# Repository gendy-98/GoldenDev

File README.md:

# UART Echo Example

(See the README.md file in the upper level 'examples' directory for more information about examples.)

This example demonstrates how to utilize UART interfaces of ESP32 by echoing back to the sender any data received on
UART1.

## How to use example

### Hardware Required

The example can be run on any ESP32 development board connected to a PC with a single USB cable for flashing and
monitoring. The external interface should have 3.3V outputs. You may use e.g. 3.3V compatible USB-to-Serial dongle.

### Setup the Hardware

Connect the external serial interface to the ESP32 board as follows.

  | ESP32 Interface | #define | ESP32 Pin | External UART Pin |
  | --- | --- | --- | --- |
  | Transmit Data (TxD) | ECHO_TEST_TXD | GPIO4 | RxD |
  | Receive Data (RxD) | ECHO_TEST_RXD | GPIO5 | TxD |
  | Ground | n/a | GND | GND |

Optionally, you can set-up and use a serial interface that has RTS and CTS signals in order to verify that the
hardware control flow works. Connect the extra signals according to the following table, configure both extra pins in
the example code by replacing existing `UART_PIN_NO_CHANGE` macros with the appropriate pin numbers and configure
UART1 driver to use the hardware flow control by setting `.flow_ctrl = UART_HW_FLOWCTRL_CTS_RTS` and adding
`.rx_flow_ctrl_thresh = 122`.

  | ESP32 Interface | #define | ESP32 Pin | External UART Pin |
  | --- | --- | --- | --- |
  | Request to Send (RTS) | ECHO_TEST_RTS | GPIO18 | CTS |
  | Clear to Send (CTS) | ECHO_TEST_CTS | GPIO19 | RTS |

### Configure the project

```
idf.py menuconfig
```

### Build and Flash

Build the project and flash it to the board, then run monitor tool to view serial output:

```
idf.py -p PORT flash monitor
```

(To exit the serial monitor, type ``Ctrl-]``.)

See the Getting Started Guide for full steps to configure and use ESP-IDF to build projects.

## Example Output

Type some characters in the terminal connected to the external serial interface. As result you should see echo in the
terminal which is used for flashing and monitoring. You can verify if the echo indeed comes from ESP32 by
disconnecting either `TxD` or `RxD` pin: no characters will appear when typing.

## Troubleshooting

You are not supposed to see the echo in the terminal which is used for flashing and monitoring, but in the other one
which is connected to UART1.

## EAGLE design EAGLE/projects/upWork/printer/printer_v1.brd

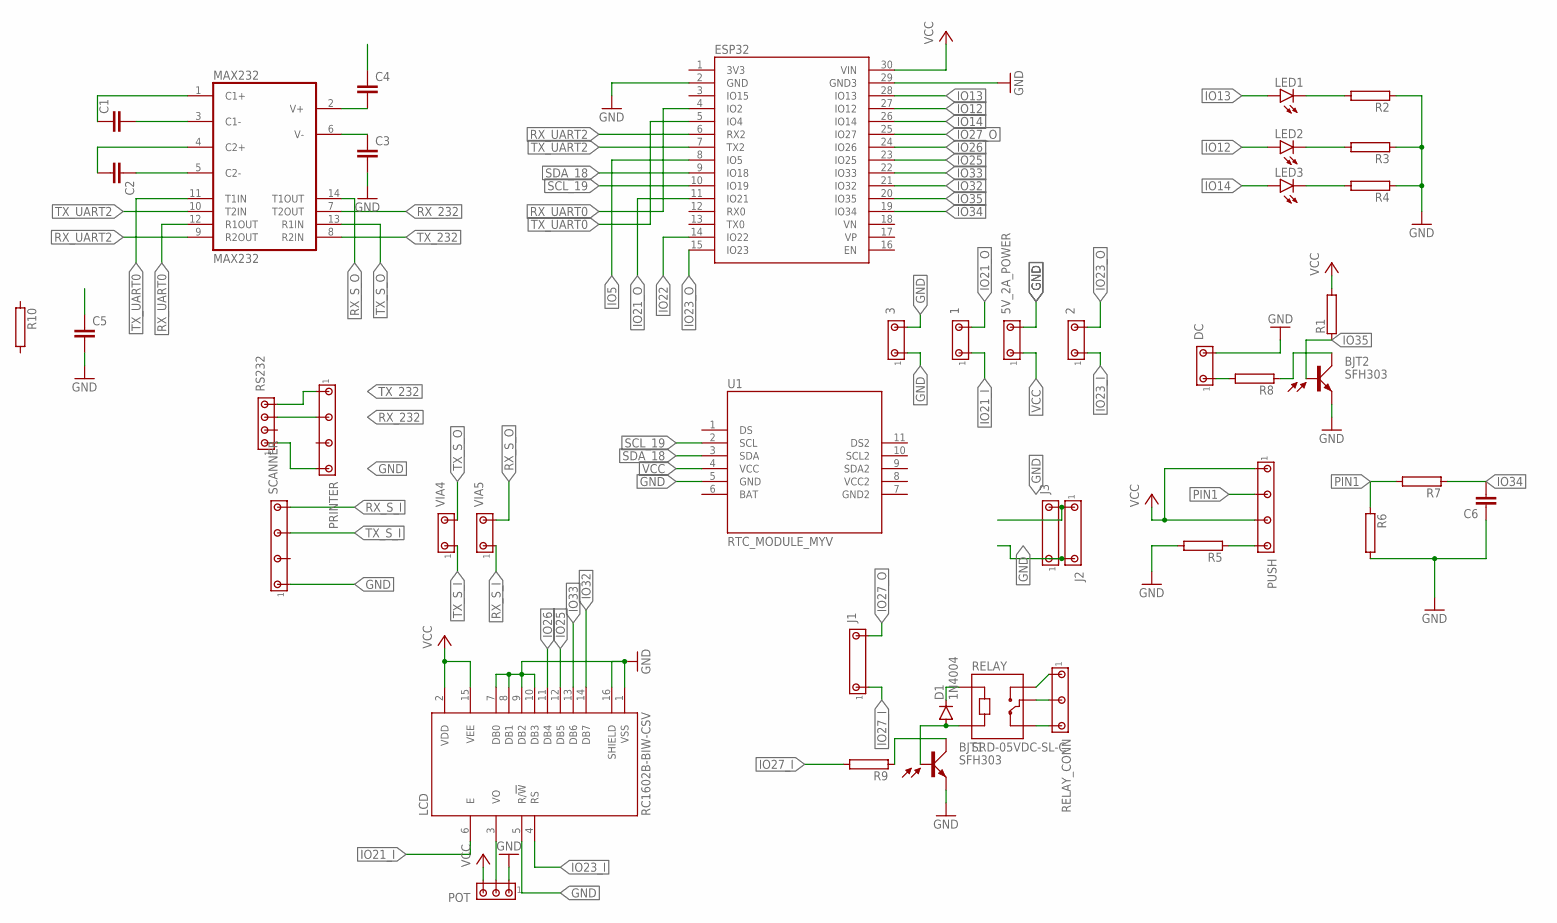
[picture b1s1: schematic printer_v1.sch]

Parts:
1, 2, 3, 5V_2A_POWER: MTA03-100_MYV; 10X03MTA_MYV
BJT1, BJT2: SFH303
C1, C2, C3, C4, C5, C6: C-EU025-024X044; C025-024X044
D1: 1N4004; DO41-10
DC: MTA03-100_MYV; 10X03MTA_MYV
ESP32: MODULE_ESP32_MYV; MODULE_ESP32-DEVKITC-MYV
J1, J2, J3: MTA02-LARGE_MYVSPACE1; 10X02MTA_LARGE_MYV
LCD: RC1602B-BIW-CSV; LCD_RC1602B-BIW-CSV
LED1, LED2, LED3: LED3MM
MAX232: MAX232; DIL16
POT: MTA03-100; 10X03MTA
PRINTER: MTA07-100_MYV; 10X07MTA_MYV
PUSH: MTA07-100_MYV; 10X07MTA_MYV
R1, R2, R3, R4, R5, R6, R7, R8, R9, R10: RHPS58; HPS58
RELAY: SRD-05VDC-SL-C; RELAY_SRD-05VDC-SL-C
RELAY_CONN: MTA05-156_MYVSPACE1; 10X05MTA_MYV
RS232: MTA04-100; 10X04MTA
SCANNER: MTA07-100_MYV; 10X07MTA_MYV
U1: RTC_MODULE_MYV; RTC_MYV
VIA4, VIA5: MTA03-100_MYV; 10X03MTA_MYV

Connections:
3V3: ESP32.1 (3V3)
GND: 3.1, 3.3, 5V_2A_POWER.3, BJT1.1 (E), BJT2.1 (E), C3.2, C5.2, C6.1, DC.3, ESP32.2 (GND), ESP32.29 (GND3), J2.1, J2.5, J3.1, J3.5, LCD.1 (VSS), LCD.5 (R/!W), LCD.7 (DB0), LCD.8 (DB1), LCD.9 (DB2), LCD.10 (DB3), LCD.16 (SHIELD), MAX232.15 (GND), POT.1, PRINTER.7, R2.1, R3.1, R4.1, R5.2, R6.2, RS232.1, SCANNER.1, U1.5 (GND)
IO5: ESP32.8 (IO5)
IO12: ESP32.27 (IO12), LED2.A
IO13: ESP32.28 (IO13), LED1.A
IO14: ESP32.26 (IO14), LED3.A
IO21_I: 1.1, LCD.6 (E)
IO21_O: 1.3, ESP32.11 (IO21)
IO22: ESP32.14 (IO22)
IO23_I: 2.1, LCD.4 (RS)
IO23_O: 2.3, ESP32.15 (IO23)
IO25: ESP32.23 (IO25), LCD.12 (DB5)
IO26: ESP32.24 (IO26), LCD.11 (DB4)
IO27_I: J1.1, R9.2
IO27_O: ESP32.25 (IO27), J1.5
IO32: ESP32.21 (IO32), LCD.14 (DB7)
IO33: ESP32.22 (IO33), LCD.13 (DB6)
IO34: C6.2, ESP32.19 (IO34), R7.1
IO35: BJT2.3 (B), ESP32.20 (IO35), R1.1
unnamed: C1.1, MAX232.1 (C1+)
unnamed: C1.2, MAX232.3 (C1-)
unnamed: C2.1, MAX232.5 (C2-)
unnamed: C2.2, MAX232.4 (C2+)
unnamed: C3.1, MAX232.6 (V-)
unnamed: C4.2, MAX232.2 (V+)
unnamed: D1.C, RELAY.A1
unnamed: BJT1.2 (C), R9.1
unnamed: RELAY.NC, RELAY_CONN.5
unnamed: RELAY.COM, RELAY_CONN.3
unnamed: RELAY.NO, RELAY_CONN.1
unnamed: LED1.K (C), R2.2
unnamed: LED2.K (C), R3.2
unnamed: BJT2.2 (C), R8.1
unnamed: LED3.K (C), R4.2
unnamed: LCD.3 (VO), POT.2
unnamed: DC.1, R8.2
unnamed: BJT1.3 (B), D1.A, RELAY.A2
unnamed: PUSH.7, R5.1
PIN1: PUSH.3, R6.1, R7.2
RX_232: MAX232.7 (T2OUT), PRINTER.3, RS232.3
RX_S_I: SCANNER.7, VIA5.1
RX_S_O: MAX232.14 (T1OUT), VIA5.3
RX_UART0: ESP32.4 (IO2), MAX232.12 (R1OUT)
RX_UART2: ESP32.6 (RX2), MAX232.9 (R2OUT)
SCL_19: ESP32.10 (IO19), U1.2 (SCL)
SDA_18: ESP32.9 (IO18), U1.3 (SDA)
TX_232: MAX232.8 (R2IN), PRINTER.1, RS232.4
TX_S_I: SCANNER.5, VIA4.1
TX_S_O: MAX232.13 (R1IN), VIA4.3
TX_UART0: ESP32.5 (IO4), MAX232.11 (T1IN)
TX_UART2: ESP32.7 (TX2), MAX232.10 (T2IN)
VCC: 5V_2A_POWER.1, ESP32.30 (VIN), LCD.2 (VDD), LCD.15 (VEE), MAX232.16 (VCC), POT.3, PUSH.1, PUSH.5, R1.2, U1.4 (VCC)

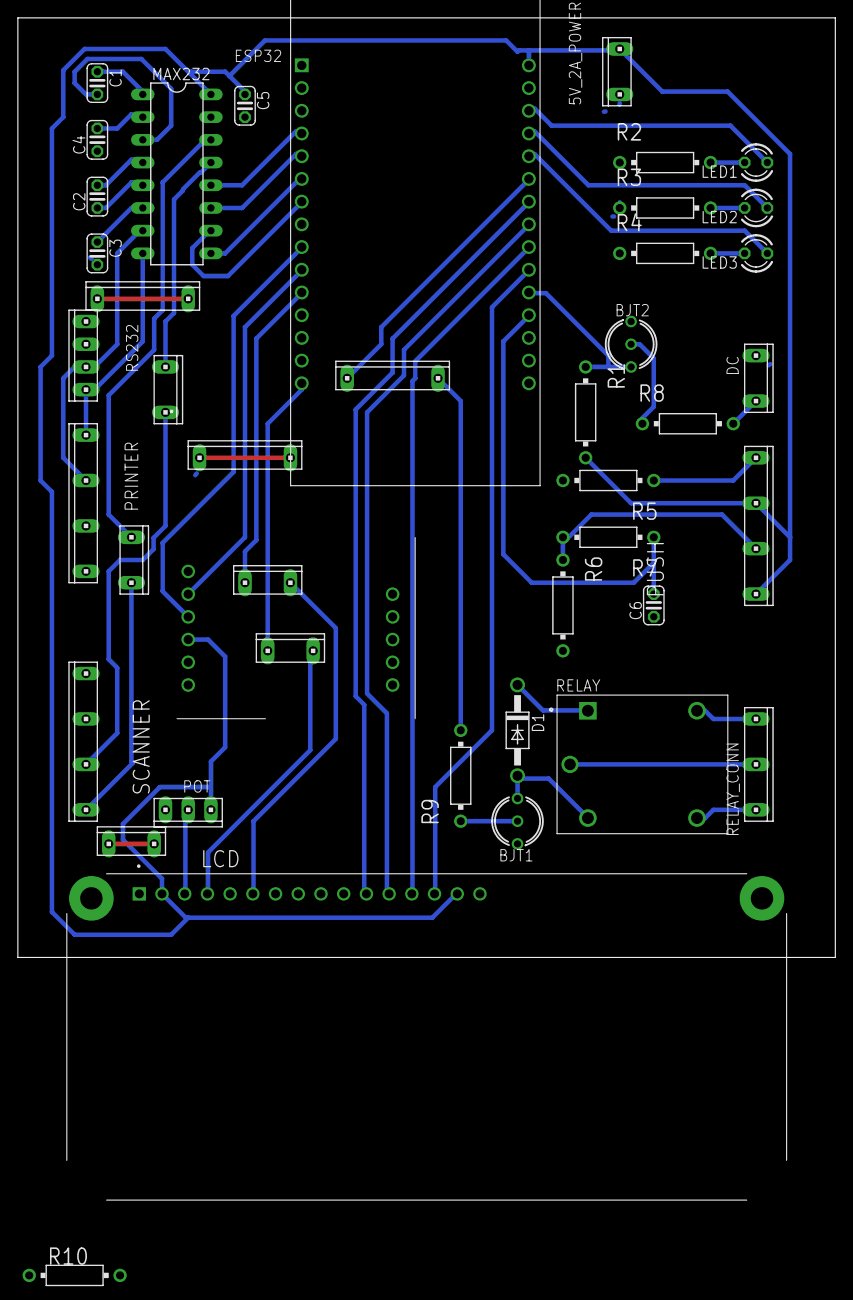
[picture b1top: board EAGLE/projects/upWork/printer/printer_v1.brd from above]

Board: 2 copper layers, 91.4 x 105.1 mm, 43 parts (0 on the bottom side), 49 nets.

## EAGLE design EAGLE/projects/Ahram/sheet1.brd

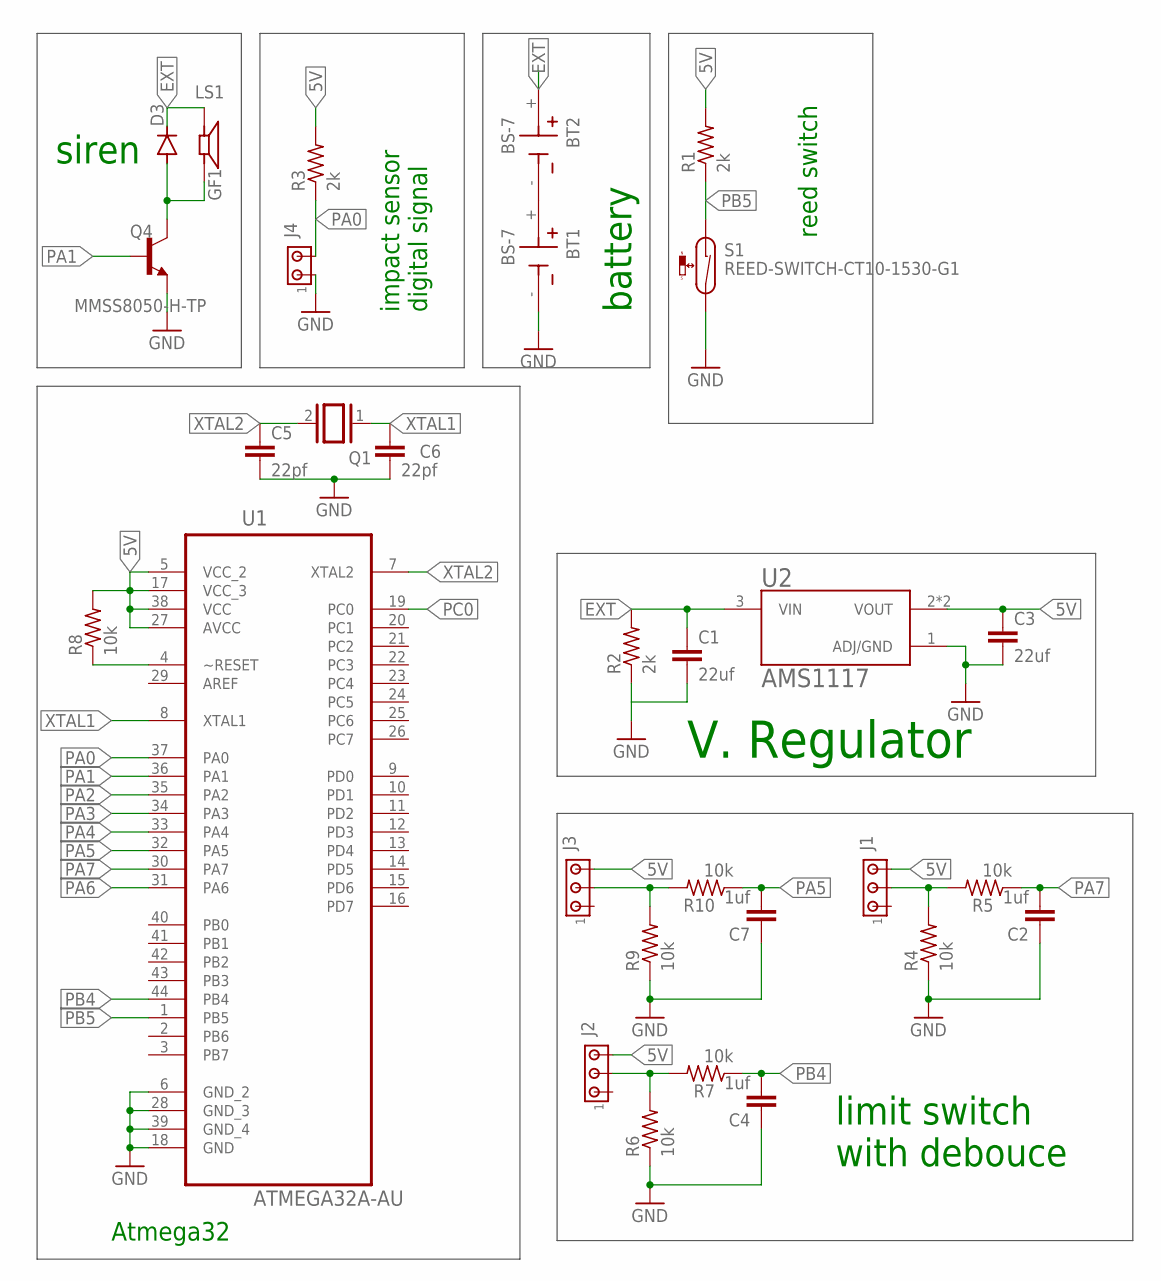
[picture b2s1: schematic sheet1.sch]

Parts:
BT1, BT2: BS-7; BAT_BS-7
C1, C3: 22uf; C1206
C2, C4, C7: 1uf; C1206
C5, C6: 22pf; C1206
D3: GF1; SMA-DO214AC
J1, J2, J3: MTA03-100; 10X03MTA
J4: MTA02-100; 10X02MTA
LS1: CEP-1152; CUI_CEP-1152
Q1: XTAL/S; QS
Q4: MMSS8050-H-TP; TRANS_MMSS8050-H-TP
R1, R2, R3: 2k; R1206
R4, R5, R6, R7, R8, R9, R10: 10k; R1206
S1: REED-SWITCH-CT10-1530-G1; CT10-G1
U1: ATMEGA32A-AU; QFP80P1200X1200X120-44N
U2: AMS1117; SOT229P700X180-4N

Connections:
5V: C3.1, J1.3, J2.3, J3.3, R1.2, R3.2, R8.2, U1.5 (VCC_2), U1.17 (VCC_3), U1.27 (AVCC), U1.38 (VCC), U2.2 (VOUT), U2.4 (VOUT)
EXT: BT2.+, C1.1, D3.K (C), LS1.1, R2.2, U2.3 (VIN)
GND: BT1.-, C1.2, C2.1, C3.2, C4.1, C5.2, C6.2, C7.1, J4.1, Q4.2 (E), R2.1, R4.1, R6.1, R9.1, S1.2, U1.6 (GND_2), U1.18 (GND), U1.28 (GND_3), U1.39 (GND_4), U2.1 (ADJ/GND)
unnamed: J1.2, R4.2, R5.2
unnamed: BT1.+, BT2.-
unnamed: R8.1, U1.4 (~RESET)
unnamed: J3.2, R9.2, R10.2
unnamed: J2.2, R6.2, R7.2
unnamed: D3.A, LS1.2, Q4.3 (C)
PA0: J4.2, R3.1, U1.37 (PA0)
PA1: Q4.1 (B), U1.36 (PA1)
PA2: U1.35 (PA2)
PA3: U1.34 (PA3)
PA4: U1.33 (PA4)
PA5: C7.2, R10.1, U1.32 (PA5)
PA6: U1.31 (PA6)
PA7: C2.2, R5.1, U1.30 (PA7)
PB4: C4.2, R7.1, U1.44 (PB4)
PB5: R1.1, S1.1, U1.1 (PB5)
PC0: U1.19 (PC0)
XTAL1: C6.1, Q1.1, U1.8 (XTAL1)
XTAL2: C5.1, Q1.2, U1.7 (XTAL2)

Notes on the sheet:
V. Regulator
siren
impact sensor digital signal
battery
limit switch with debouce
reed switch
Atmega32

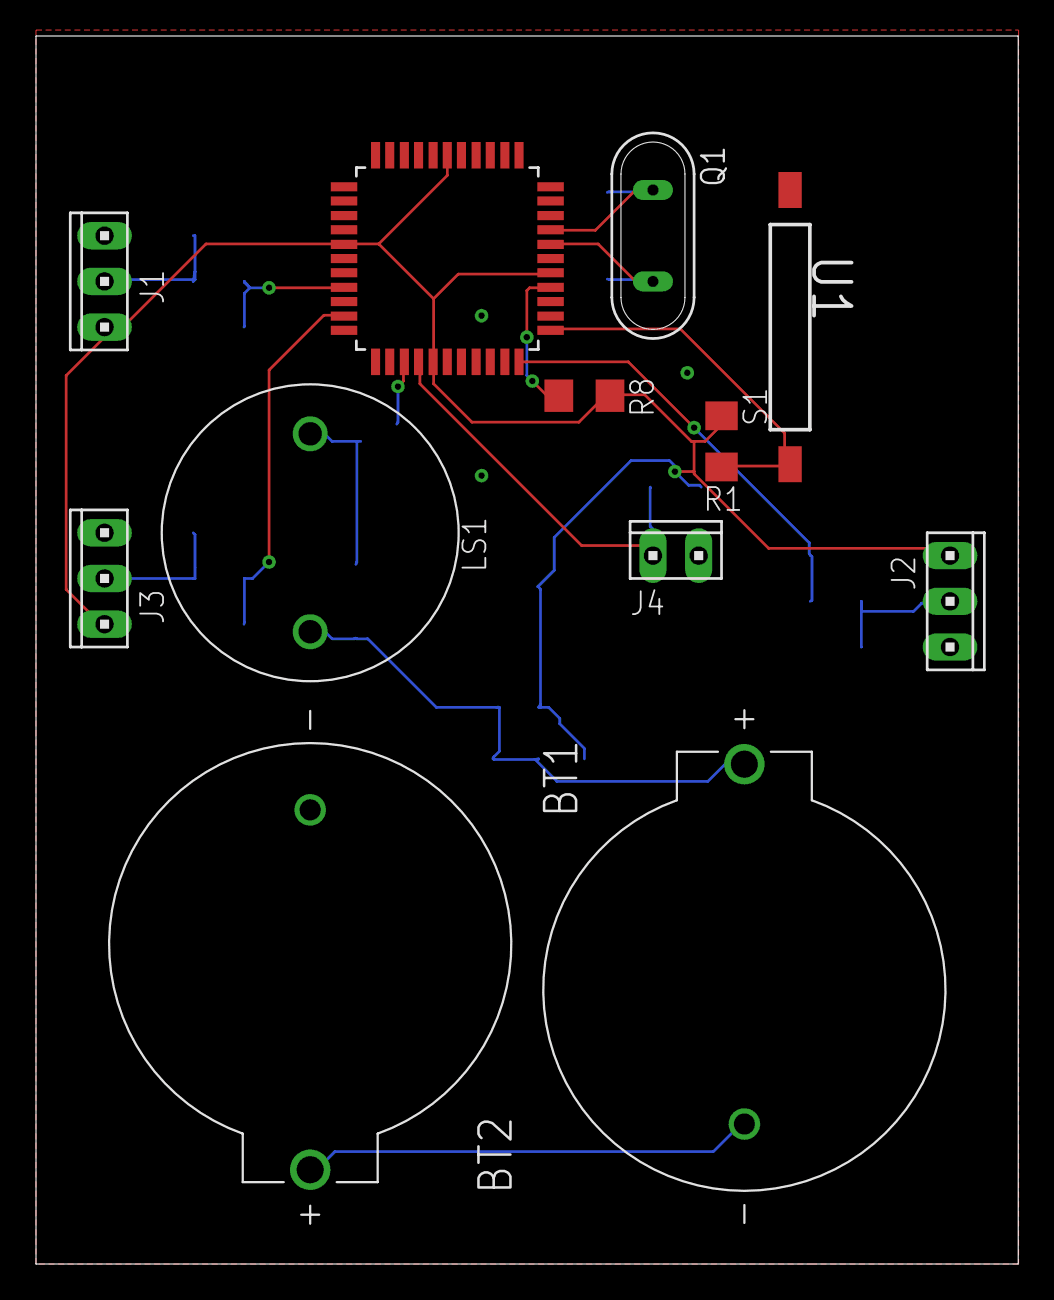
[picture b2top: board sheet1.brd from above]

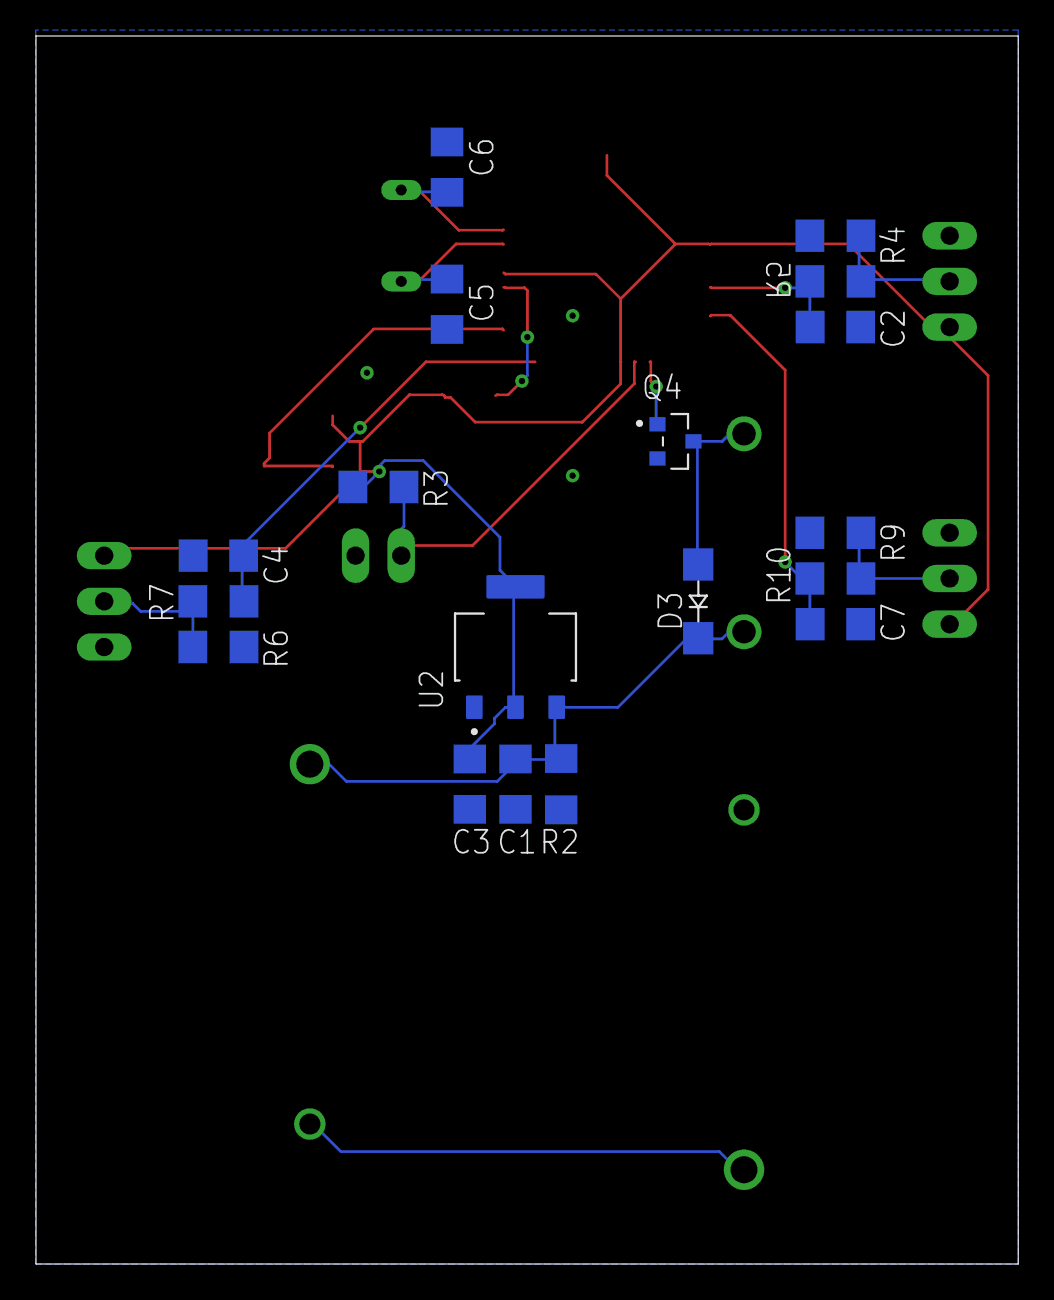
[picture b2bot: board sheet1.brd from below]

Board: 2 copper layers, 54.6 x 68.2 mm, 30 parts (18 on the bottom side), 17 nets.

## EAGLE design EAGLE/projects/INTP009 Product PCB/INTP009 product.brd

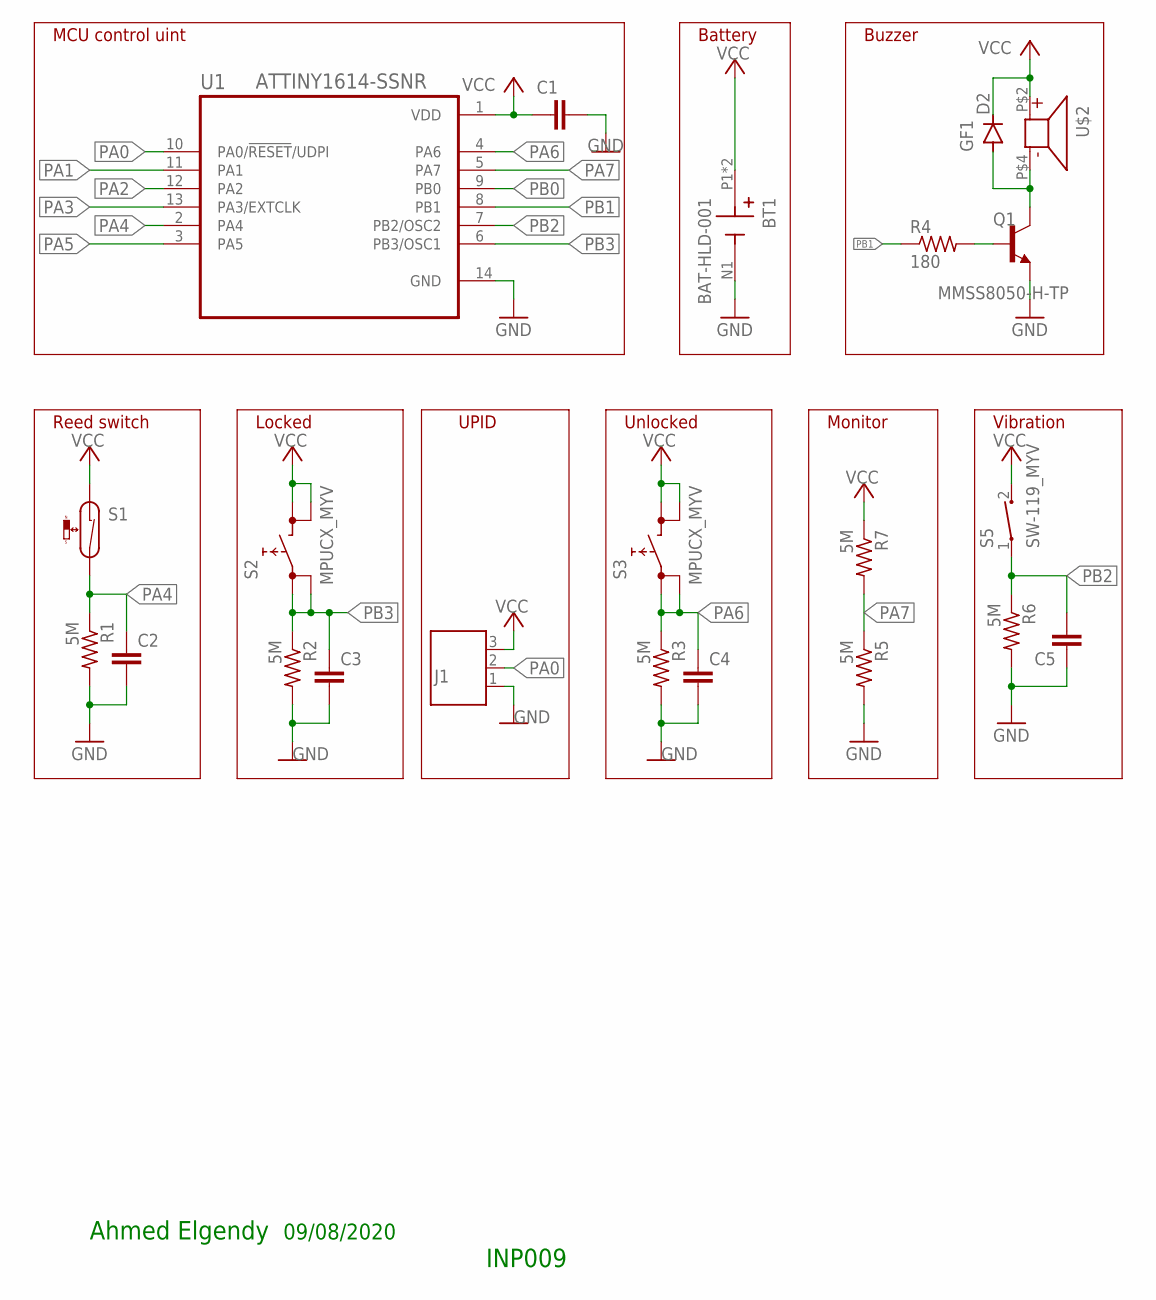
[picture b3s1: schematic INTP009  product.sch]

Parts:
BT1: BAT-HLD-001; BAT_BAT-HLD-001
C1, C2, C3, C4, C5: C-EUC0805K; C0805K
D2: GF1; SMA-DO214AC
J1: 691508110303
Q1: MMSS8050-H-TP; TRANS_MMSS8050-H-TP
R1, R2, R3, R5, R6, R7: 5M; M0805
R4: 180; M0805
S1: RI80SMDM-MYV; RI80SMDM-0510-J1
S2, S3: MPUCX_MYV
S5: SW-119_MYV; SW-119
U1: ATTINY1614-SSNR; SOIC127P600X175-14N
U$2: ST-A03BH_MYV

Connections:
GND: BT1.N1 (-), C1.2, C2.2, C3.2, C4.2, C5.1, J1.1, Q1.2 (E), R1.2, R2.2, R3.2, R5.2, R6.2, U1.14 (GND)
unnamed: D2.A, Q1.3 (C), U$2.P$4 (2)
unnamed: Q1.1 (B), R4.2
PA0: J1.2, U1.10 (PA0/!RESET!/UDPI)
PA1: U1.11 (PA1)
PA2: U1.12 (PA2)
PA3: U1.13 (PA3/EXTCLK)
PA4: C2.1, R1.1, S1.P$2 (2), U1.2 (PA4)
PA5: U1.3 (PA5)
PA6: C4.1, R3.1, S3.1, S3.2, U1.4 (PA6)
PA7: R5.1, R7.2, U1.5 (PA7)
PB0: U1.9 (PB0)
PB1: R4.1, U1.8 (PB1)
PB2: C5.2, R6.1, S5.1, U1.7 (PB2/OSC2)
PB3: C3.1, R2.1, S2.1, S2.2, U1.6 (PB3/OSC1)
VCC: BT1.P1 (+), BT1.P2 (+), C1.1, D2.K (C), J1.3, R7.1, S1.P$1 (1), S2.3, S2.4, S3.3, S3.4, S5.2, U1.1 (VDD), U$2.P$2 (1)

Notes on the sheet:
Ahmed Elgendy
09/08/2020
INP009
MCU control uint
Reed switch
Locked
Unlocked
Battery
Vibration
Buzzer
Monitor
UPID

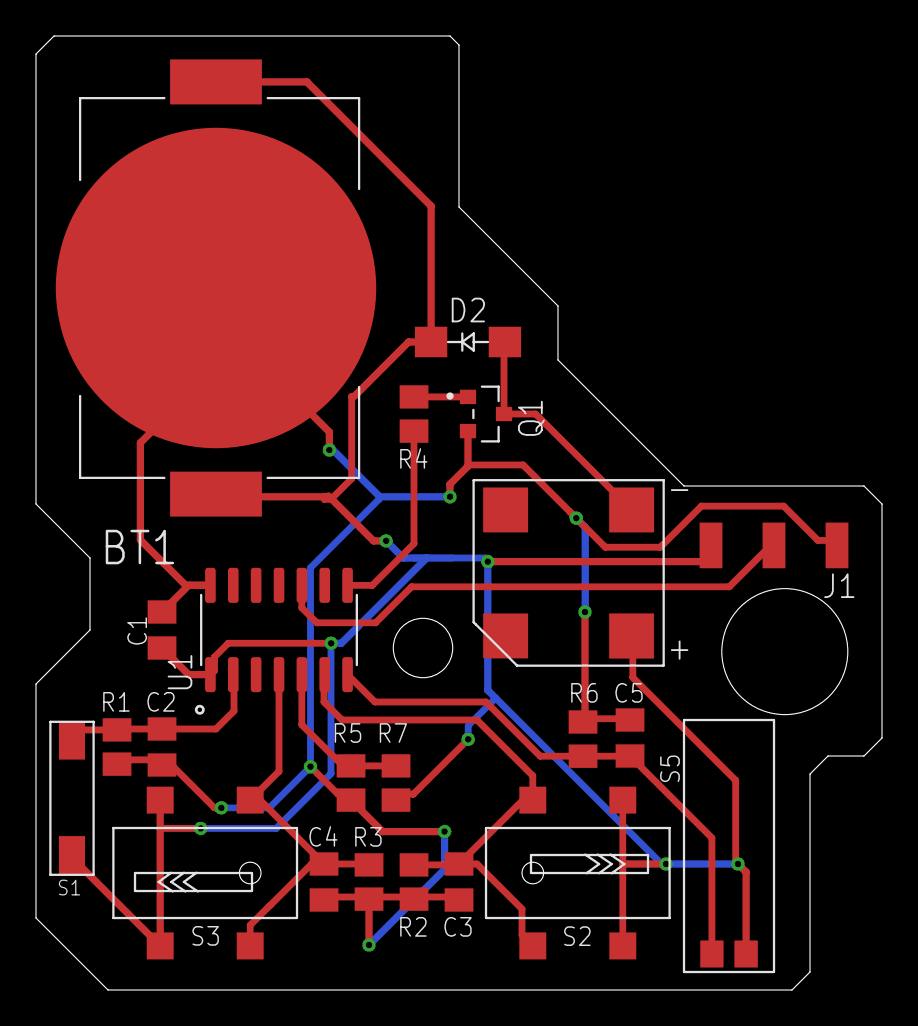
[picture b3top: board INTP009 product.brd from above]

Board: 2 copper layers, 47.0 x 53.0 mm, 22 parts (0 on the bottom side), 11 nets.

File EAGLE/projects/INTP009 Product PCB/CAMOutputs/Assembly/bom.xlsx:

Qty | Value | Device | Package | Parts | Description | ARROW_ELECTRONICS-PURCHASE-URL | AVAILABILITY | DESCRIPTION | DIGIKEY-PURCHASE-URL | MF | MOUSER-PURCHASE-URL | MP | PACKAGE | POPULARITY | PRICE | SPICEPREFIX
1 |  | 691508110303 | 691508110303 | J1 | WR-TBL Terminal block - serie 5081 - 3 Pins;=>Code : Con_TBL_Screw_PClamp_3.50_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
2 | 100nf | C-EUC0805K | C0805K | C1, C2, C3, C4, C5 | CAPACITOR, European symbol |  |  |  |  |  |  |  |  | 52 |  | C
3 | 180ohm | R-US_M0805 | M0805 | R4 | RESISTOR, American symbol |  |  |  |  |  |  |  |  | 45 |  | R
4 | 5M | R-US_M0805 | M0805 | R1, R2, R3, R5, R6, R7 | RESISTOR, American symbol |  |  |  |  |  |  |  |  | 45 |  | R
5 | ATTINY1614-SSNR | ATTINY1614-SSNR | SOIC127P600X175-14N | U1 | 20MHz, SOIC, 85C, Green, 14 SOIC .150in T/R | https://snapeda.com/shop?store=Arrow+Electronics&id=4817174 | Unavailable | IC MCU 8BIT 16KB FLASH 14SOIC | https://snapeda.com/shop?store=DigiKey&id=4817174 | Microchip Technology | https://snapeda.com/shop?store=Mouser&id=4817174 | ATTINY1614-SSNR | None |  | None
6 | BAT-HLD-001 | BAT-HLD-001 | BAT_BAT-HLD-001 | BT1 | Battery Retainer Coin, 20.0mm 1 Cell SMD (SMT) Tab Buy Part |  | Good | Battery Holder 1 Cells Phosphor Bronze Bulk | https://snapeda.com/shop?store=DigiKey&id=184402 | Linx Technologies | https://snapeda.com/shop?store=Mouser&id=184402 | BAT-HLD-001 | None |  | None
7 | GF1 | GF1 | SMA-DO214AC | D2 | DIODE |  |  |  |  |  |  |  |  | 2
8 | MMSS8050-H-TP | MMSS8050-H-TP | TRANS_MMSS8050-H-TP | Q1 | MMSS8050-H Series 25 V 1.5 A NPN Silicon Plastic-Encapsulate Transistor-SOT-23 |  | Unavailable | Bipolar _BJT_ Transistor NPN 25V 1.5A 100MHz 625mW Surface Mount SOT-23 |  | Micro Commercial |  | MMSS8050-H-TP | SOT-23 Micro Commercial |  | None
9 | MPUCX_MYV | MPUCX_MYV | MPUCX_MYV | S2, S3
10 | RI80SMDM-MYV | RI80SMDM-MYV | RI80SMDM-0510-J1 | S1
11 | ST-A03BH_MYV | ST-A03BH_MYV | ST-A03BH_MYV | U$2
12 | SW-119_MYV | SW-119_MYV | SW-119 | S5

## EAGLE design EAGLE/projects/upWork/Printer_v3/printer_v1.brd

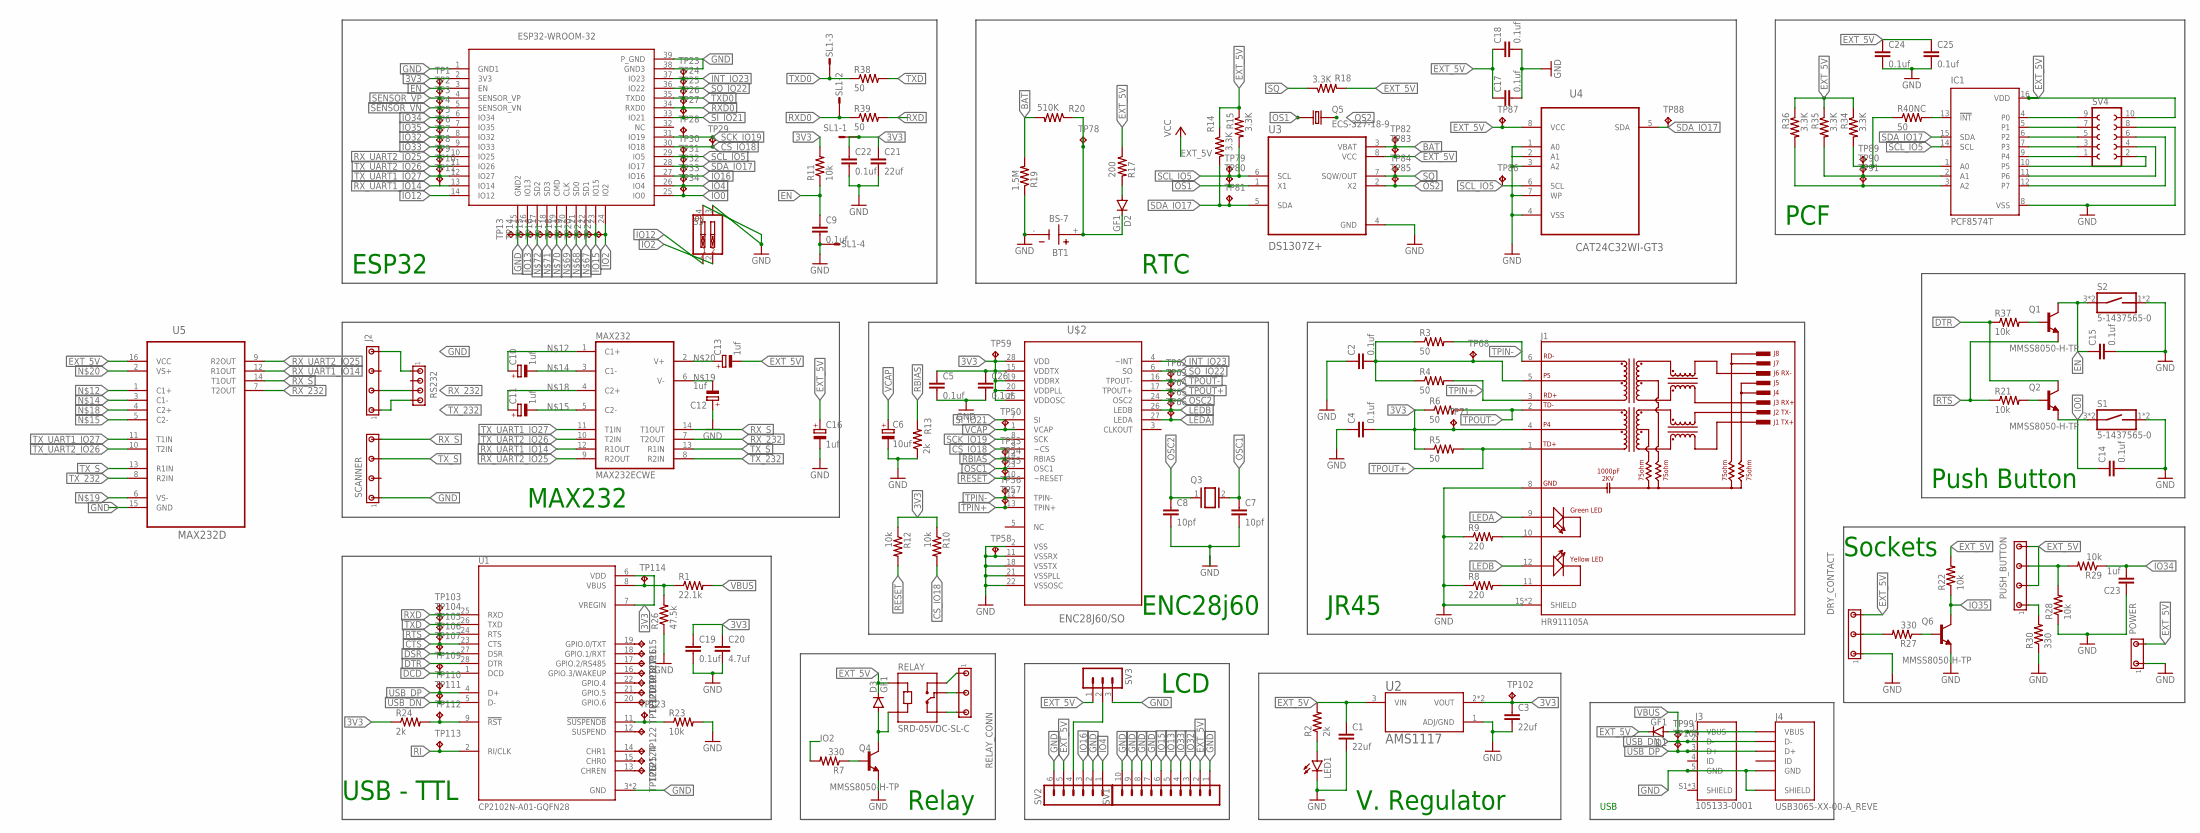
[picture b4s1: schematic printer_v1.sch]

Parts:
BT1: BS-7; BAT_BS-7
C1, C3, C21: 22uf; C1206
C2, C4, C5, C9, C14, C15, C17, C18, C19, C22, C24, C25, C26: 0.1uf; C1206
C6: 10uf; 153CLV-0405
C7, C8: 10pf; C1206
C10, C11, C12, C13, C16: 1uf; 153CLV-0405
C20: 4.7uf; C1206
C23: 1uf; C1206
D1, D2, D3: GF1; SMA-DO214AC
DRY_CONTACT: MTA05-156_MYVSPACE1; 10X05MTA_MYV
IC1: PCF8574T; SO16W
J1: HR911105A; HANRUN_HR911105A
J2: MTA07-100_MYV; 10X07MTA_MYV
J3: 105133-0001; MOLEX_105133-0001
J4: USB3065-XX-00-A_REVE; GCT_USB3065-XX-00-A_REVE
LED1: LEDSML0603; SML0603
MAX232: MAX232ECWE; SO16L
POWER: MTA03-100_MYV; 10X03MTA_MYV
PUSH_BUTTON: MTA07-100_MYV; 10X07MTA_MYV
Q1, Q2, Q4, Q6: MMSS8050-H-TP; TRANS_MMSS8050-H-TP
Q3: XTAL/S; QS
Q5: ECS-327-18-9; XTAL_ECS-160-18-9X
R1: 22.1k; R1206
R2, R13, R24: 2k; R1206
R3, R4, R5, R6: 50; R1206
R7, R27, R30: 330; R1206
R8, R9: 220; R1206
R10, R11, R12, R21, R22, R23, R28, R29, R37: 10k; R0805
R14, R15, R18, R34, R35, R36: 3.3K; R1206
R17: 200; R1206
R19: 1.5M; R1206
R20: 510K; R1206
R26: 47.5k; R1206
R38, R39, R40NC: 50; R0402
RELAY: SRD-05VDC-SL-C; RELAY_SRD-05VDC-SL-C
RELAY_CONN: MTA05-156_MYVSPACE1; 10X05MTA_MYV
RS232: MTA04-100; 10X04MTA
S1, S2: 5-1437565-0; SW_5-1437565-0
S3: SW_DIP-2; EDG-02
SCANNER: MTA07-100_MYV; 10X07MTA_MYV
SL1: M04S; 04P
SV1: MA10-1
SV2: MA06-1
SV3: MA03-1
SV4: FE05-2
TP1, TP2, TP3, TP4, TP5, TP6, TP7, TP8, TP9, TP10, TP11, TP13, TP14, TP15, TP16, TP17, TP18, TP19, TP20, TP21, TP22, TP23, TP24, TP25, TP26, TP27, TP28, TP29, TP30, TP31, TP32, TP33, TP34, TP50, TP53, TP54, TP55, TP56, TP57, TP58, TP59, TP62, TP63, TP64, TP65, TP66, TP68, TP71, TP78, TP79, TP80, TP81, TP82, TP83, TP84, TP85, TP86, TP87, TP88, TP89, TP90, TP91, TP99, TP100, TP102, TP103, TP104, TP105, TP106, TP107, TP109, TP110, TP111, TP112, TP113, TP114, TP115, TP116, TP117, TP118, TP119, TP120, TP121, TP122, TP123, TP124, TP125, TP126: TPTP06R; TP06R
U1: CP2102N-A01-GQFN28; QFN50P500X500X80-29N
U2: AMS1117; SOT229P700X180-4N
U3: DS1307Z+; SOIC127P600X175-8N
U4: CAT24C32WI-GT3; SOIC127P600X175-8N
U5: MAX232D; SOIC127P600X175-16N
U$2: ENC28J60/SO; SOIC127P1034X264-28N
U$3: ESP32-WROOM-32

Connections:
3V3: C3.1, C4.2, C5.1, C19.1, C20.1, C21.1, C22.1, C26.1, J1.4, R5.1, R6.1, R10.1, R11.2, R12.1, R24.1, SL1.1, TP59.TP, TP71.TP, TP102.TP, U1.6 (VDD), U1.7 (VREGIN), U2.2 (VOUT), U2.4 (VOUT), U$2.15 (VDDTX), U$2.19 (VDDRX), U$2.20 (VDDPLL), U$2.25 (VDDOSC), U$2.28 (VDD), U$3.2 (3V3)
BAT: R19.2, R20.2, TP82.TP, U3.3 (VBAT)
CS_IO18: R10.2, TP29.TP, U$2.9 (~CS), U$3.30 (IO18)
CTS: TP106.TP, U1.23 (CTS)
DCD: TP109.TP, U1.1 (DCD)
DSR: TP107.TP, U1.27 (DSR)
DTR: Q2.3 (C), R37.1, U1.28 (DTR)
EN: C9.1, C15.1, Q1.3 (C), R11.1, S2.3 (1), S2.4 (1), TP1.TP, U$3.3 (EN)
EXT_5V: C1.1, C13.-, C16.+, C17.1, C18.1, C24.1, C25.1, D1.K (C), D3.K (C), DRY_CONTACT.5, IC1.16 (VDD), MAX232.16 (VCC), POWER.3, PUSH_BUTTON.3, PUSH_BUTTON.7, R2.2, R14.1, R15.1, R17.1, R18.2, R22.2, R34.1, R35.1, R36.1, RELAY.A1, SV1.2, SV2.5, SV3.1, SV4.10, TP83.TP, TP87.TP, U2.3 (VIN), U3.8 (VCC), U4.8 (VCC), U5.16 (VCC)
GND: BT1.-, C1.2, C2.1, C3.2, C4.1, C5.2, C6.-, C7.2, C8.2, C9.2, C12.+, C14.2, C15.2, C16.-, C17.2, C18.2, C19.2, C20.2, C21.2, C22.2, C23.1, C24.2, C25.2, C26.2, DRY_CONTACT.1, IC1.8 (VSS), J1.8 (GND), J1.15 (SHIELD), J1.16 (SHIELD), J2.7, J3.5 (GND), J4.5 (GND), J4.6 (SHIELD), J4.7 (SHIELD), J4.8 (SHIELD), J4.9 (SHIELD), LED1.C, MAX232.15 (GND), POWER.1, Q4.2 (E), Q6.2 (E), R8.1, R9.1, R13.1, R19.1, R23.2, R26.1, R28.1, R30.1, RS232.1, S1.1 (2), S1.2, S2.1 (2), S2.2, S3.3, S3.4, SCANNER.1, SL1.4, SV1.1, SV1.7, SV1.8, SV1.9, SV1.10, SV2.2, SV2.6, SV3.3, SV4.8, TP13.TP, TP58.TP, U1.3 (GND), U1.29 (GND), U2.1 (ADJ/GND), U3.4 (GND), U4.1 (A0), U4.2 (A1), U4.3 (A2), U4.4 (VSS), U4.7 (WP), U5.15 (GND), U$2.2 (VSS), U$2.11 (VSSRX), U$2.18 (VSSTX), U$2.21 (VSSPLL), U$2.22 (VSSOSC), U$3.1 (GND1), U$3.15 (GND2), U$3.38 (GND3), U$3.39 (P_GND)
INT_IO23: TP23.TP, U$2.4 (~INT), U$3.37 (IO23)
IO0: C14.1, Q2.2 (E), S1.3 (1), S1.4 (1), TP34.TP, U$3.25 (IO0)
IO2: R7.2, S3.2, TP22.TP, U$3.24 (IO2)
IO4: SV2.1, TP33.TP, U$3.26 (IO4)
IO12: S3.1, U$3.14 (IO12)
IO13: SV1.5, TP14.TP, U$3.16 (IO13)
IO15: SV1.6, TP21.TP, U$3.23 (IO15)
IO16: SV2.3, TP32.TP, U$3.27 (IO16)
IO32: SV1.3, TP6.TP, U$3.8 (IO32)
IO33: SV1.4, TP7.TP, U$3.9 (IO33)
IO34: C23.2, R29.1, TP4.TP, U$3.6 (IO34)
IO35: Q6.3 (C), R22.1, TP5.TP, U$3.7 (IO35)
LEDA: J1.9 (GA), TP66.TP, U$2.27 (LEDA)
LEDB: J1.12 (YA), TP65.TP, U$2.26 (LEDB)
unnamed: LED1.A, R2.1
unnamed: Q1.1 (B), R37.2
unnamed: Q2.1 (B), R21.2
unnamed: R1.1, R26.2, TP114.TP, U1.8 (VBUS)
unnamed: SV2.4, SV3.2
unnamed: R23.1, TP123.TP, U1.11 (!SUSPENDB)
unnamed: J1.11 (YC), R8.2
unnamed: C2.2, J1.5, R3.1, R4.1, TP68.TP
unnamed: J1.10 (GC), R9.2
unnamed: TP115.TP, U1.19 (GPIO.0/TXT)
unnamed: TP116.TP, U1.18 (GPIO.1/RXT)
unnamed: C10.+, MAX232.1 (C1+), U5.1 (C1+)
unnamed: TP117.TP, U1.17 (GPIO.2/RS485)
unnamed: C10.-, MAX232.3 (C1-), U5.3 (C1-)
unnamed: C11.-, MAX232.5 (C2-), U5.5 (C2-)
unnamed: R24.2, TP112.TP, U1.9 (!RST)
unnamed: TP118.TP, U1.16 (GPIO.3/WAKEUP)
unnamed: C11.+, MAX232.4 (C2+), U5.4 (C2+)
unnamed: C12.-, MAX232.6 (V-), U5.6 (VS-)
unnamed: C13.+, MAX232.2 (V+), U5.2 (VS+)
unnamed: RELAY.NC, RELAY_CONN.5
unnamed: RELAY.COM, RELAY_CONN.3
unnamed: IC1.9 (P4), SV4.1
unnamed: IC1.13 (!INT), R40NC.2
unnamed: TP119.TP, U1.22 (GPIO.4)
unnamed: RELAY.NO, RELAY_CONN.1
unnamed: D3.A, Q4.3 (C), RELAY.A2
unnamed: D2.A, R17.2
unnamed: BT1.+, D2.K (C), R20.1, TP78.TP
unnamed: TP120.TP, U1.21 (GPIO.5)
unnamed: TP121.TP, U1.20 (GPIO.6)
unnamed: Q6.1 (B), R27.1
unnamed: PUSH_BUTTON.5, R28.2, R29.2
unnamed: TP122.TP, U1.12 (SUSPEND)
unnamed: DRY_CONTACT.3, R27.2
unnamed: IC1.7 (P3), SV4.3
unnamed: IC1.6 (P2), SV4.5
unnamed: IC1.5 (P1), SV4.7
unnamed: TP124.TP, U1.14 (CHR1)
unnamed: PUSH_BUTTON.1, R30.2
unnamed: TP125.TP, U1.15 (CHR0)
unnamed: TP126.TP, U1.13 (CHREN)
unnamed: IC1.4 (P0), SV4.9
unnamed: IC1.10 (P5), SV4.2
unnamed: IC1.1 (A0), R34.2, R40NC.1, TP89.TP
unnamed: IC1.2 (A1), R35.2, TP90.TP
unnamed: IC1.3 (A2), R36.2, TP91.TP
unnamed: IC1.11 (P6), SV4.4
unnamed: IC1.12 (P7), SV4.6
unnamed: Q4.1 (B), R7.1
unnamed: TP20.TP, U$3.22 (SD1)
unnamed: TP19.TP, U$3.21 (SD0)
unnamed: TP18.TP, U$3.20 (CLK)
unnamed: TP17.TP, U$3.19 (CMD)
unnamed: TP16.TP, U$3.18 (SD3)
unnamed: TP15.TP, U$3.17 (SD2)
OS1: Q5.1, TP80.TP, U3.1 (X1)
OS2: Q5.2, TP85.TP, U3.2 (X2)
OSC1: C7.1, Q3.2, TP54.TP, U$2.23 (OSC1)
OSC2: C8.1, Q3.1, TP64.TP, U$2.24 (OSC2)
RBIAS: R13.2, TP53.TP, U$2.14 (RBIAS)
RESET: R12.2, TP55.TP, U$2.10 (~RESET)
RI: TP113.TP, U1.2 (RI/CLK)
RTS: Q1.2 (E), R21.1, TP105.TP, U1.24 (RTS)
RXD: R39.2, TP103.TP, U1.25 (RXD)
RXD0: R39.1, SL1.2, TP26.TP, U$3.34 (RXD0)
RX_232: J2.3, MAX232.7 (T2OUT), RS232.3, U5.7 (T2OUT)
RX_S: MAX232.14 (T1OUT), SCANNER.7, U5.14 (T1OUT)
RX_UART1_IO14: MAX232.12 (R1OUT), TP11.TP, U5.12 (R1OUT), U$3.13 (IO14)
RX_UART2_IO25: MAX232.9 (R2OUT), TP8.TP, U5.9 (R2OUT), U$3.10 (IO25)
SCK_IO19: TP28.TP, U$2.8 (SCK), U$3.31 (IO19)
SCL_IO5: IC1.14 (SCL), R15.2, TP30.TP, TP79.TP, TP86.TP, U3.6 (SCL), U4.6 (SCL), U$3.29 (IO5)
SDA_IO17: IC1.15 (SDA), R14.2, TP31.TP, TP81.TP, TP88.TP, U3.5 (SDA), U4.5 (SDA), U$3.28 (IO17)
SENSOR_VN: TP3.TP, U$3.5 (SENSOR_VN)
SENSOR_VP: TP2.TP, U$3.4 (SENSOR_VP)
SI_IO21: TP27.TP, U$2.7 (SI), U$3.33 (IO21)
SO_IO22: TP24.TP, U$2.6 (SO), U$3.36 (IO22)
SQ: R18.1, TP84.TP, U3.7 (SQW/OUT)
TPIN+: J1.3 (RD+), R4.2, TP57.TP, U$2.13 (TPIN+)
TPIN-: J1.6 (RD-), R3.2, TP56.TP, U$2.12 (TPIN-)
TPOUT+: J1.1 (TD+), R5.2, TP63.TP, U$2.17 (TPOUT+)
TPOUT-: J1.2 (TD-), R6.2, TP62.TP, U$2.16 (TPOUT-)
TXD: R38.2, TP104.TP, U1.26 (TXD)
TXD0: R38.1, SL1.3, TP25.TP, U$3.35 (TXD0)
TX_232: J2.1, MAX232.8 (R2IN), RS232.4, U5.8 (R2IN)
TX_S: MAX232.13 (R1IN), SCANNER.5, U5.13 (R1IN)
TX_UART1_IO27: MAX232.11 (T1IN), TP10.TP, U5.11 (T1IN), U$3.12 (IO27)
TX_UART2_IO26: MAX232.10 (T2IN), TP9.TP, U5.10 (T2IN), U$3.11 (IO26)
USB_DN: J3.2 (D-), J4.2 (D-), TP99.TP, TP111.TP, U1.5 (D-)
USB_DP: J3.3 (D+), J4.3 (D+), TP100.TP, TP110.TP, U1.4 (D+)
VBUS: D1.A, J3.1 (VBUS), J4.1 (VBUS), R1.2
VCAP: C6.+, TP50.TP, U$2.1 (VCAP)

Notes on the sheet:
PCF
ESP32
RTC
Push Button
JR45
ENC28j60
MAX232
USB - TTL
Relay
LCD
V. Regulator
USB
Sockets

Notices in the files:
parts and their libraries:
Wurth_Elektronik_Electromechanic_Termina: Copyright: Würth Elektronik
crystal-geyer_V1_0: Copyright: Geyer-Electronic
